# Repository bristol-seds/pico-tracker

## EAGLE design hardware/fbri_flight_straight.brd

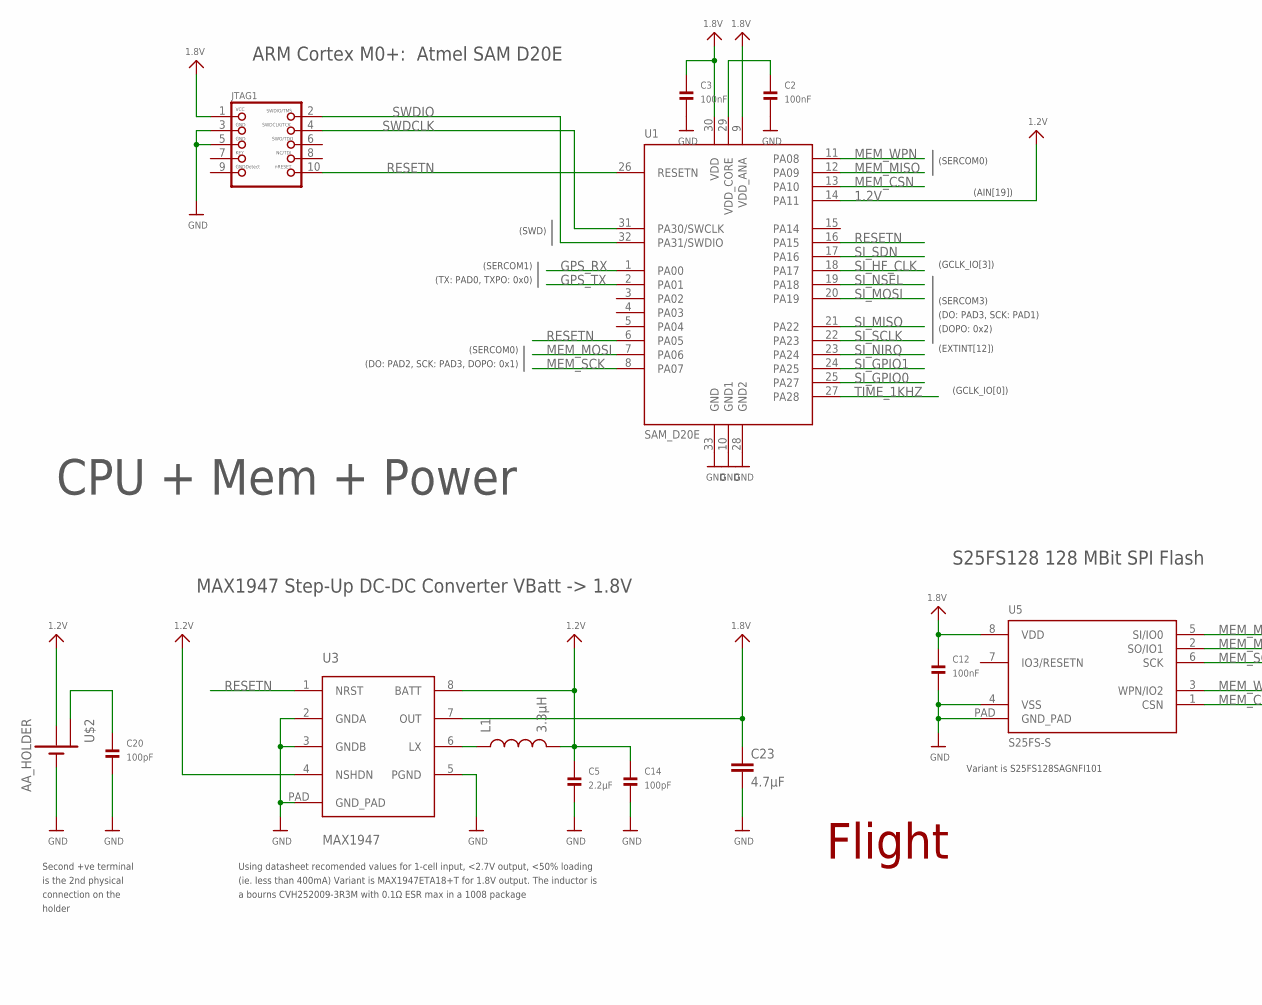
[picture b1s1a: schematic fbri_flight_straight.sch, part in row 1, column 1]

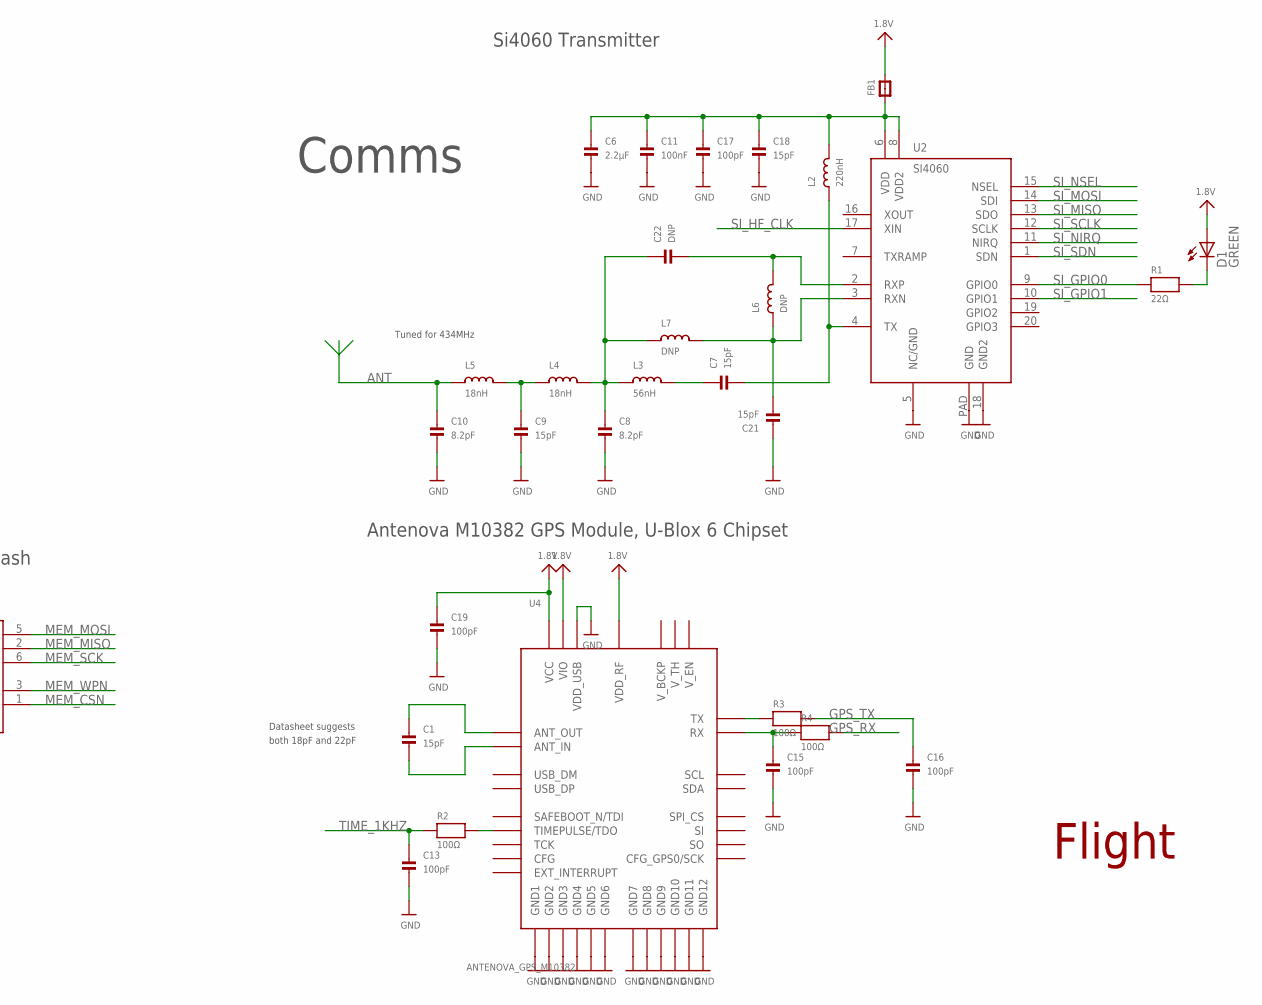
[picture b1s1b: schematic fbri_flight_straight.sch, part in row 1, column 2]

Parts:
C1, C7, C9, C18, C21: 15pF; _0402
C2, C3, C11, C12: 100nF; _0402
C5, C6: 2.2µF; _0402
C8, C10: 8.2pF; _0402
C13, C14, C15, C16, C17, C19, C20: 100pF; _0402
C22: DNP; _0402
C23: 4.7µF; C0603K
D1: GREEN; CHIPLED_0603
FB1: FERRITE_0402; _0402
JTAG1: JTAG-CORTEXM3SMT; 2X05_1.27MM_SMT
L1: 3.3µH; 1007
L2: 220nH; _0402
L3: 56nH; _0402
L4, L5: 18nH; _0402
L6, L7: DNP; _0402
R1: 22Ω; _0402
R2, R3, R4: 100Ω; _0402
U1: SAM_D20E; QFN32_5MM
U2: SI4060; QFN20
U3: MAX1947; TDFN8
U4: ANTENOVA_GPS_M10382
U5: S25FS-S; WSON8
U$2: AA_HOLDER; AA

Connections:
1.2V: C5.1, C14.1, L1.2, U1.14 (PA11), U3.4 (NSHDN), U3.8 (BATT), U$2.+2 (+)
1.8V: C3.1, C12.1, C19.1, C23.1, D1.A, FB1.2, JTAG1.1, U1.9 (VDD_ANA), U1.30 (VDD), U3.7 (OUT), U4.5_VIO (VIO), U4.25_VDD_RF (VDD_RF), U4.27_VCC (VCC), U5.8 (VDD)
ANT: C10.1, L5.1
AN_GPS_RX: C15.1, R4.1, U4.13_RX (RX)
AN_GPS_TX: R3.1, U4.11_TX (TX)
FILTER1: C8.1, C22.1, L3.1, L4.2, L7.1
FILTER2: C9.1, L4.1, L5.2
GND: C2.2, C3.2, C5.2, C6.2, C8.2, C9.2, C10.2, C11.2, C12.2, C13.2, C14.2, C15.2, C16.2, C17.2, C18.2, C19.2, C20.2, C21.1, C23.2, JTAG1.3, JTAG1.5, U1.10 (GND1), U1.28 (GND2), U1.33 (GND), U2.5 (NC/GND), U2.18 (GND2), U2.PAD (GND), U3.2 (GNDA), U3.3 (GNDB), U3.5 (PGND), U3.PAD (GND_PAD), U4.2_GND (GND1), U4.4_GND (GND2), U4.14_GND (GND3), U4.17_GND (GND4), U4.21_GND (GND5), U4.24_GND (GND6), U4.26_GND (GND7), U4.28_GND (GND8), U4.32_VDD_USB (VDD_USB), U4.33_GND (GND9), U4.34_GND (GND10), U4.35_GND (GND11), U4.36_GND (GND12), U5.4 (VSS), U5.PAD (GND_PAD), U$2.-1 (-), U$2.-2 (-)
GPS_ANT_IN: C1.2, U4.1_ANT_IN (ANT_IN)
GPS_ANT_OUT: C1.1, U4.3_ANT_OUT (ANT_OUT)
GPS_RX: R4.2, U1.1 (PA00)
GPS_TX: C16.1, R3.2, U1.2 (PA01)
LED_RES: D1.C, R1.2
LX: L1.1, U3.6 (LX)
MEM_CSN: U1.13 (PA10), U5.1 (CSN)
MEM_MISO: U1.12 (PA09), U5.2 (SO/IO1)
MEM_MOSI: U1.7 (PA06), U5.5 (SI/IO0)
MEM_SCK: U1.8 (PA07), U5.6 (SCK)
MEM_WPN: U1.11 (PA08), U5.3 (WPN/IO2)
unnamed: C20.1, U$2.+1 (+2)
RADIO_VDD: C6.1, C11.1, C17.1, C18.1, FB1.1, L2.2, U2.6 (VDD), U2.8 (VDD2)
RESETN: JTAG1.10, U1.6 (PA05), U1.16 (PA15), U1.26 (RESETN), U3.1 (NRST)
RF_OUT: C7.2, L2.1, U2.4 (TX)
RXN: C21.2, L6.1, L7.2, U2.3 (RXN)
RXP: C22.2, L6.2, U2.2 (RXP)
SI_GPIO0: R1.1, U1.25 (PA27), U2.9 (GPIO0)
SI_GPIO1: U1.24 (PA25), U2.10 (GPIO1)
SI_HF_CLK: U1.18 (PA17), U2.17 (XIN)
SI_MISO: U1.21 (PA22), U2.13 (SDO)
SI_MOSI: U1.20 (PA19), U2.14 (SDI)
SI_NIRQ: U1.23 (PA24), U2.11 (NIRQ)
SI_NSEL: U1.19 (PA18), U2.15 (NSEL)
SI_SCLK: U1.22 (PA23), U2.12 (SCLK)
SI_SDN: U1.17 (PA16), U2.1 (SDN)
SWDCLK: JTAG1.4, U1.31 (PA30/SWCLK)
SWDIO: JTAG1.2, U1.32 (PA31/SWDIO)
TANK: C7.1, L3.2
TIME_1KHZ: C13.1, R2.1, U1.27 (PA28)
TIME_1KHZ_DRIVE: R2.2, U4.23_TIMEPULSE/TDO (TIMEPULSE/TDO)
VDD_CORE: C2.1, U1.29 (VDD_CORE)

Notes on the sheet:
ARM Cortex M0+: Atmel SAM D20E
(SERCOM3)
(SWD)
(GCLK_IO[0])
Using datasheet recomended values for 1-cell input, <2.7V output, <50% loading (ie. less than 400mA) Variant is MAX1947ETA18+T for 1.8V output. The inductor is a bourns CVH252009-3R3M with 0.1Ω ESR max in a 1008 package
(SERCOM0)
(EXTINT[12])
(DO: PAD3, SCK: PAD1)
(DOPO: 0x2)
(DO: PAD2, SCK: PAD3, DOPO: 0x1)
(GCLK_IO[3])
(SERCOM1)
(TX: PAD0, TXPO: 0x0)
MAX1947 Step-Up DC-DC Converter VBatt -> 1.8V
(AIN[19])
S25FS128 128 MBit SPI Flash
Variant is S25FS128SAGNFI101
Antenova M10382 GPS Module, U-Blox 6 Chipset
Si4060 Transmitter
Tuned for 434MHz
CPU + Mem + Power
Comms
Flight
Datasheet suggests both 18pF and 22pF
Second +ve terminal is the 2nd physical connection on the holder

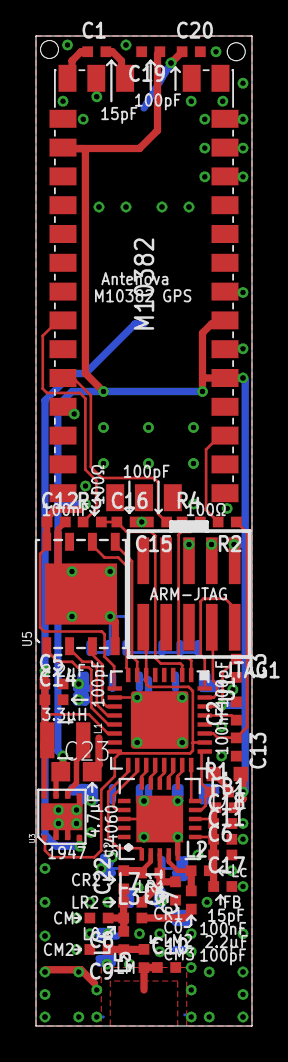
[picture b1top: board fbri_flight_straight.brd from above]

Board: 2 copper layers, 12.0 x 55.0 mm, 42 parts (1 on the bottom side), 40 nets.

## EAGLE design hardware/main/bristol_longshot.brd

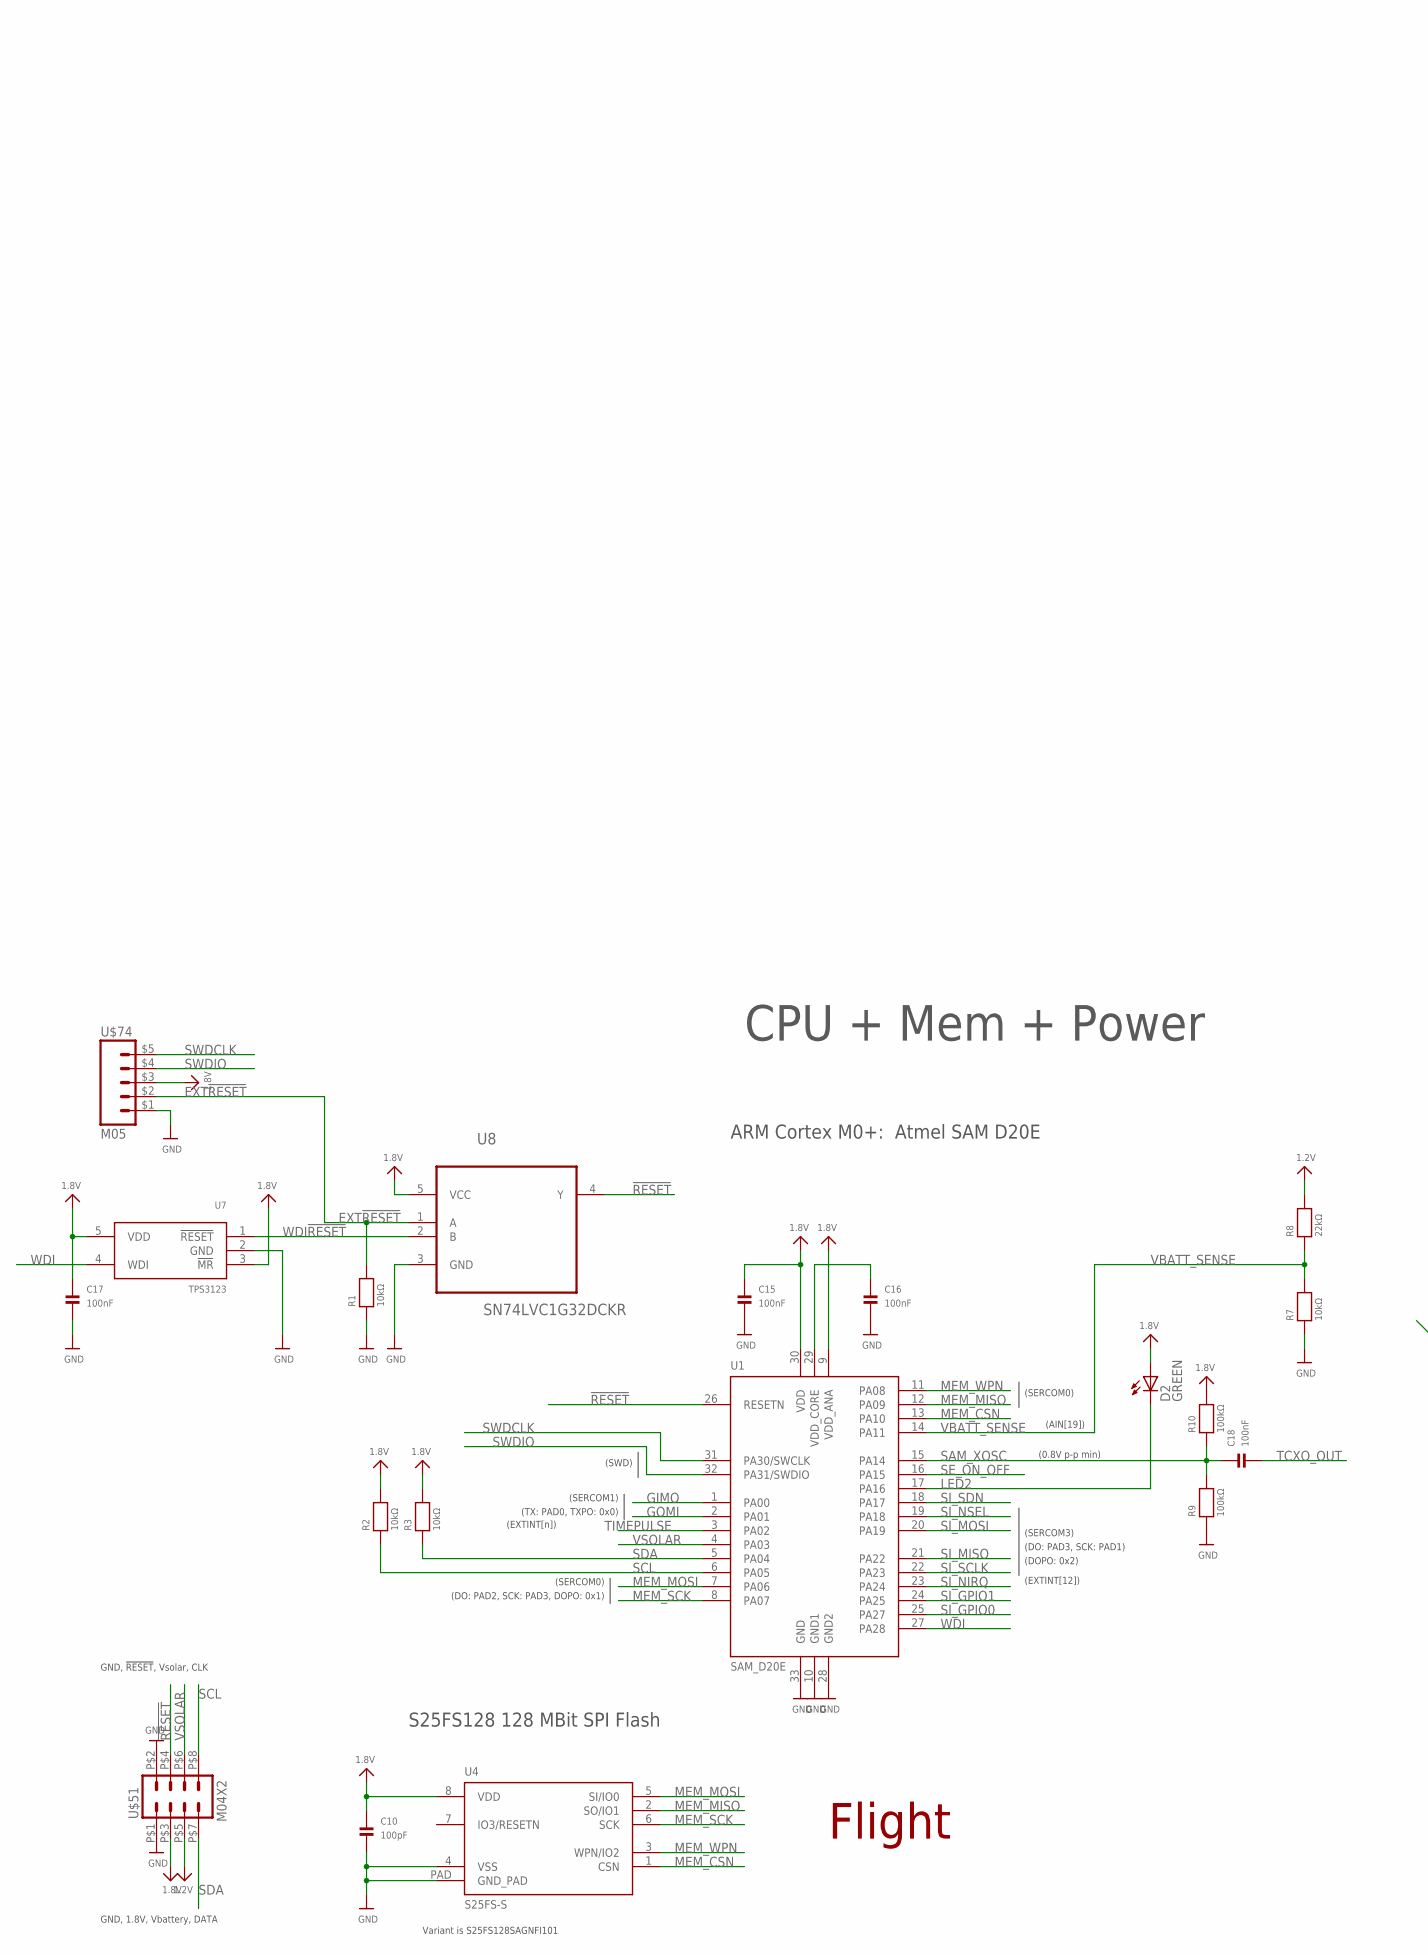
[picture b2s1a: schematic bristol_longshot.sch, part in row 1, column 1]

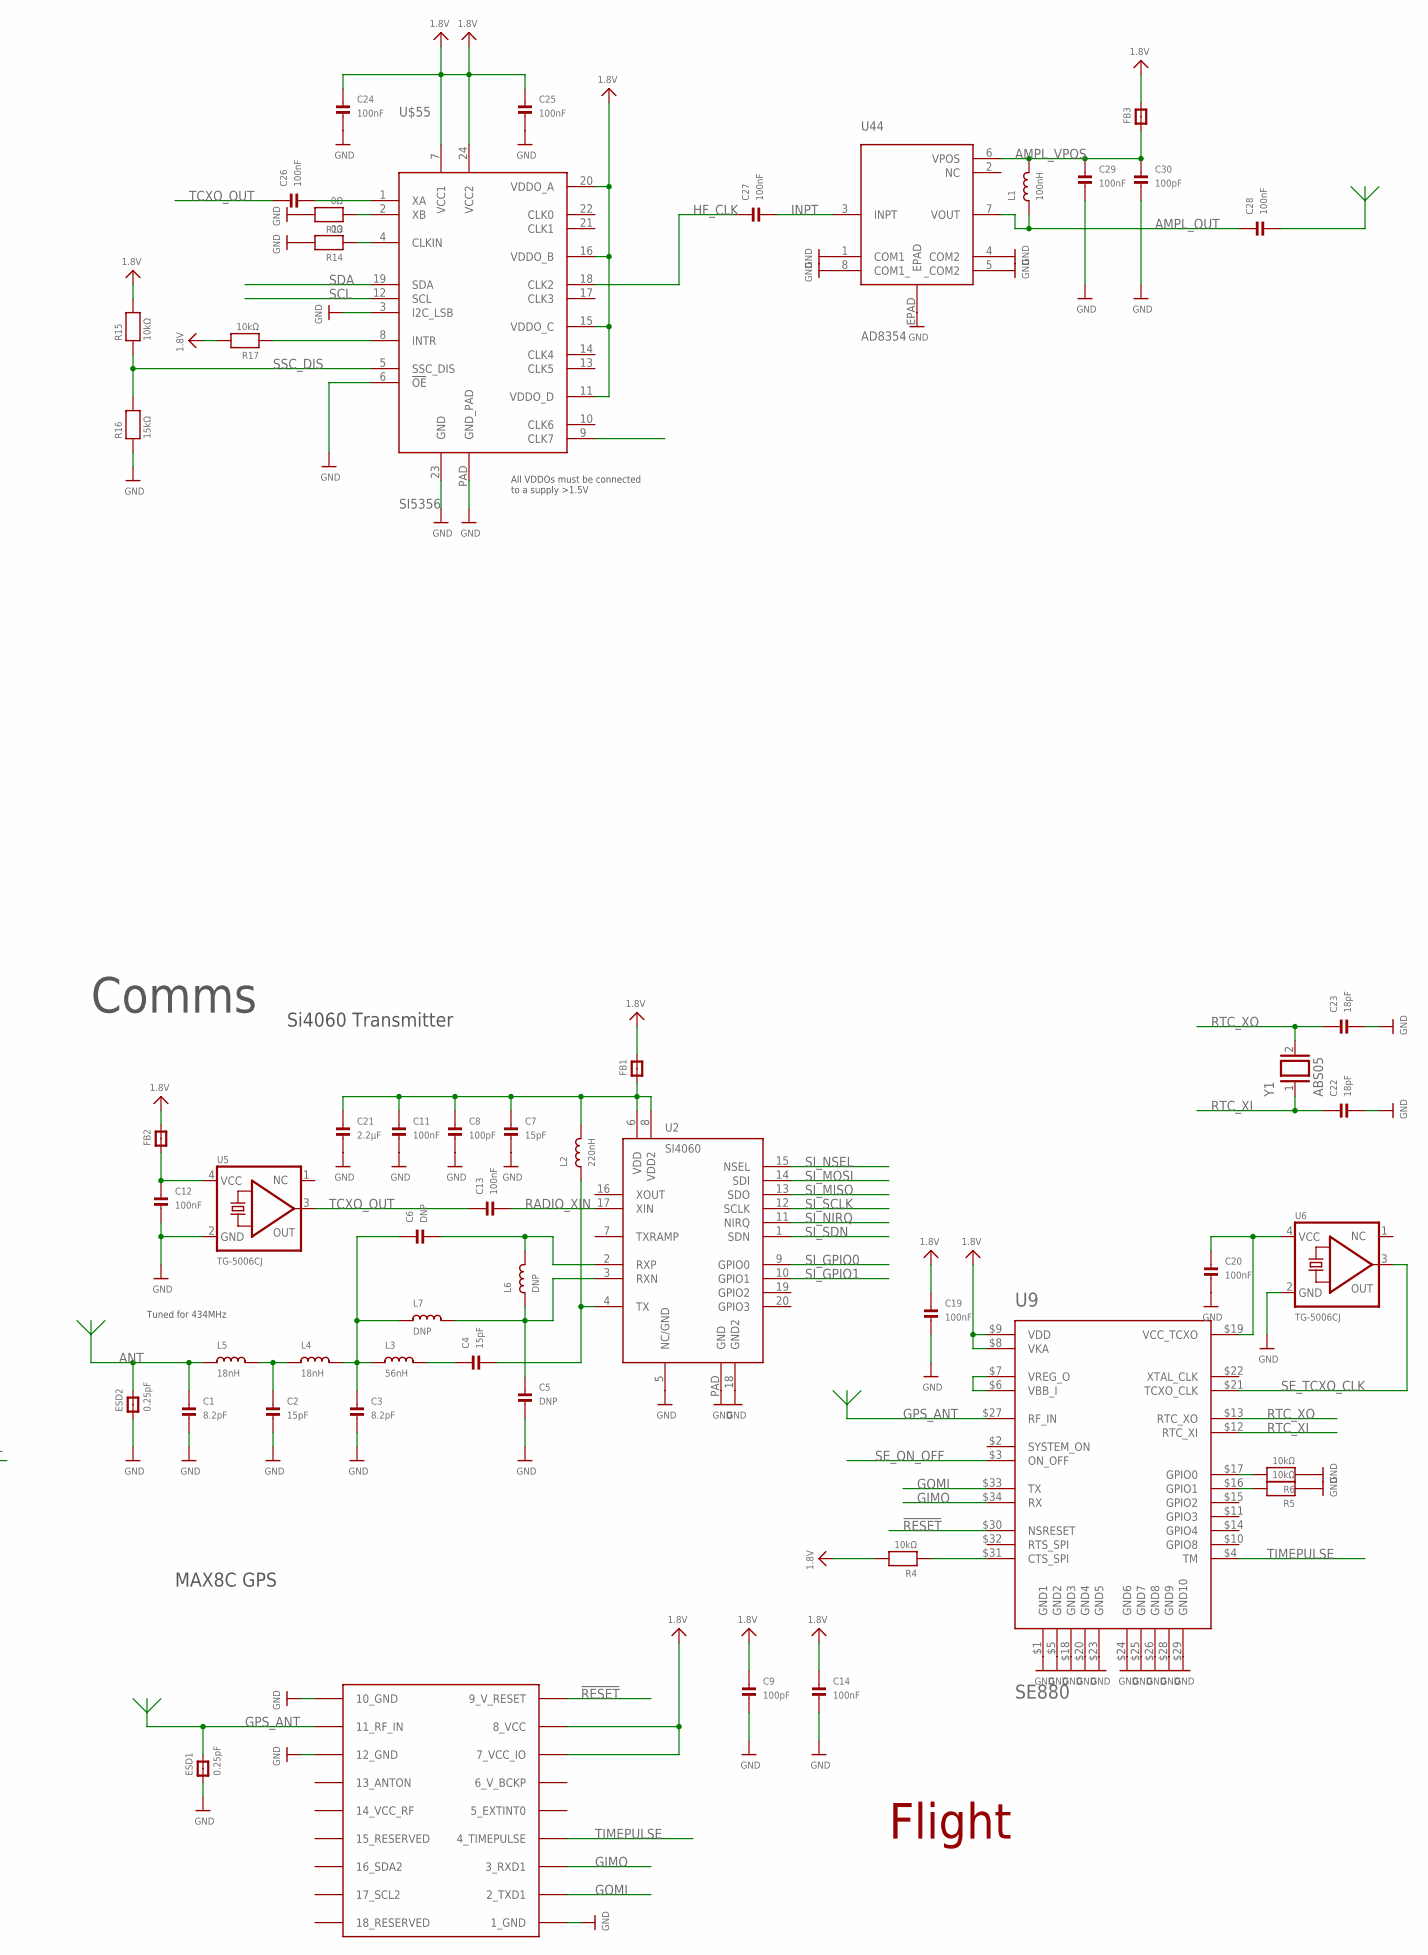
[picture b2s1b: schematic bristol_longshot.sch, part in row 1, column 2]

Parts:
C1, C3: 8.2pF; _0402
C2, C4, C7: 15pF; _0402
C5, C6: DNP; _0402
C8, C9, C10, C30: 100pF; _0402
C11, C12, C13, C14, C15, C16, C17, C18, C19, C20, C24, C25, C26, C27, C28, C29: 100nF; _0402
C21: 2.2µF; _0402
C22, C23: 18pF; _0402
D2: GREEN; CHIPLED_0603
ESD1, ESD2: 0.25pF; _0603MP
FB1, FB2, FB3: FERRITE_0402; _0402
L1: 100nH; _0402
L2: 220nH; _0402
L3: 56nH; _0402
L4, L5: 18nH; _0402
L6, L7: DNP; _0402
R1, R2, R3, R4, R5, R6, R7, R15, R17: 10kΩ; _0402
R8: 22kΩ; _0402
R9, R10: 100kΩ; _0402
R13, R14: 0Ω; _0402
R16: 15kΩ; _0402
U1: SAM_D20E; QFN32_5MM
U2: SI4060; QFN20
U3: UBLOX_MAX
U4: S25FS-S; WSON8
U5, U6: TG-5006CJ; TC-5006CJ
U7: TPS3123; SOT23-5
U8: SN74LVC1G32DCKR; SOT65P210X110-5N
U9: SE880
U44: AD8354; LFCSP_VD_8
U$51: M04X2
U$55: SI5356; QFN24_4MM
U$74: M05; M05_SIDE
Y1: ABS05

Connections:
1.2V: R8.2, U$51.P$5 (5)
1.8V: C9.1, C10.1, C14.1, C15.1, C17.1, C19.1, C24.1, C25.1, D2.A, FB1.2, FB2.2, FB3.2, R2.2, R3.2, R4.2, R10.2, R15.2, R17.2, U1.9 (VDD_ANA), U1.30 (VDD), U3.7_VCC_IO, U3.8_VCC, U4.8 (VDD), U7.3 (!MR), U7.5 (VDD), U8.5 (VCC), U9.$8 (VKA), U9.$9 (VDD), U$51.P$3 (3), U$55.7 (VCC1), U$55.11 (VDDO_D), U$55.15 (VDDO_C), U$55.16 (VDDO_B), U$55.20 (VDDO_A), U$55.24 (VCC2), U$74.$3 (3)
!RESET: U1.26 (RESETN), U3.9_V_RESET, U8.4 (Y), U9.$30 (NSRESET), U$51.P$4 (4)
AMPL_OUT: C28.1, L1.1, U44.7 (VOUT)
AMPL_VPOS: C29.1, C30.1, FB3.1, L1.2, U44.6 (VPOS)
ANT: C1.1, ESD2.2, L5.1
CLKIN: R14.1, U$55.4 (CLKIN)
EXT!RESET: R1.2, U8.1 (A), U$74.$2 (2)
FILTER1: C3.1, C6.1, L3.1, L4.2, L7.1
FILTER2: C2.1, L4.1, L5.2
GIMO: U1.1 (PA00), U3.3_RXD1, U9.$34 (RX)
GND: C1.2, C2.2, C3.2, C5.2, C7.2, C8.2, C9.2, C10.2, C11.2, C12.2, C14.2, C15.2, C16.2, C17.2, C19.2, C20.2, C21.2, C22.2, C23.2, C24.2, C25.2, C29.2, C30.2, ESD1.1, ESD2.1, R1.1, R5.1, R6.1, R7.1, R9.1, R13.2, R14.2, R16.1, U1.10 (GND1), U1.28 (GND2), U1.33 (GND), U2.5 (NC/GND), U2.18 (GND2), U2.PAD (GND), U3.1_GND, U3.10_GND, U3.12_GND, U4.4 (VSS), U4.PAD (GND_PAD), U5.2 (GND), U6.2 (GND), U7.2 (GND), U8.3 (GND), U9.$1 (GND1), U9.$5 (GND2), U9.$18 (GND3), U9.$20 (GND4), U9.$23 (GND5), U9.$24 (GND6), U9.$25 (GND7), U9.$26 (GND8), U9.$28 (GND9), U9.$29 (GND10), U44.1 (COM1), U44.4 (COM2), U44.5 (_COM2), U44.8 (COM1_), U44.EPAD, U$51.P$1 (1), U$51.P$2 (2), U$55.3 (I2C_LSB), U$55.6 (!OE), U$55.23 (GND), U$55.PAD (GND_PAD), U$74.$1 (1)
GOMI: U1.2 (PA01), U3.2_TXD1, U9.$33 (TX)
GPS_ANT: ESD1.2, U3.11_RF_IN, U9.$27 (RF_IN)
HF_ANT: C28.2
HF_CLK: C27.1, U$55.18 (CLK2)
INPT: C27.2, U44.3 (INPT)
INTR: R17.1, U$55.8 (INTR)
LED2: D2.C, U1.17 (PA16)
MEM_CSN: U1.13 (PA10), U4.1 (CSN)
MEM_MISO: U1.12 (PA09), U4.2 (SO/IO1)
MEM_MOSI: U1.7 (PA06), U4.5 (SI/IO0)
MEM_SCK: U1.8 (PA07), U4.6 (SCK)
MEM_WPN: U1.11 (PA08), U4.3 (WPN/IO2)
unnamed: U9.$6 (VBB_I), U9.$7 (VREG_O)
unnamed: R6.2, U9.$17 (GPIO0)
unnamed: R4.1, U9.$31 (CTS_SPI)
unnamed: R5.2, U9.$16 (GPIO1)
RADIO_VDD: C7.1, C8.1, C11.1, C21.1, FB1.1, L2.2, U2.6 (VDD), U2.8 (VDD2)
RADIO_XIN: C13.2, U2.17 (XIN)
RF_OUT: C4.2, L2.1, U2.4 (TX)
RTC_XI: C22.1, U9.$12 (RTC_XI), Y1.1
RTC_XO: C23.1, U9.$13 (RTC_XO), Y1.2
RXN: C5.1, L6.1, L7.2, U2.3 (RXN)
RXP: C6.2, L6.2, U2.2 (RXP)
SAM_XOSC: C18.1, R9.2, R10.1, U1.15 (PA14)
SCL: R2.1, U1.6 (PA05), U$51.P$8 (8), U$55.12 (SCL)
SDA: R3.1, U1.5 (PA04), U$51.P$7 (7), U$55.19 (SDA)
SE_ON_OFF: U1.16 (PA15), U9.$3 (ON_OFF)
SE_TCXO_CLK: U6.3 (OUT), U9.$21 (TCXO_CLK)
SE_VCO_TCXO: C20.1, U6.4 (VCC), U9.$19 (VCC_TCXO)
SI_GPIO0: U1.25 (PA27), U2.9 (GPIO0)
SI_GPIO1: U1.24 (PA25), U2.10 (GPIO1)
SI_MISO: U1.21 (PA22), U2.13 (SDO)
SI_MOSI: U1.20 (PA19), U2.14 (SDI)
SI_NIRQ: U1.23 (PA24), U2.11 (NIRQ)
SI_NSEL: U1.19 (PA18), U2.15 (NSEL)
SI_SCLK: U1.22 (PA23), U2.12 (SCLK)
SI_SDN: U1.18 (PA17), U2.1 (SDN)
SSC_DIS: R15.1, R16.2, U$55.5 (SSC_DIS)
SWDCLK: U1.31 (PA30/SWCLK), U$74.$5 (5)
SWDIO: U1.32 (PA31/SWDIO), U$74.$4 (4)
TANK: C4.1, L3.2
TCXO_OUT: C13.1, C18.2, C26.1, U5.3 (OUT)
TCXO_VDD: C12.1, FB2.1, U5.4 (VCC)
TIMEPULSE: U1.3 (PA02), U3.4_TIMEPULSE, U9.$4 (TM)
VBATT_SENSE: R7.2, R8.1, U1.14 (PA11)
VDD_CORE: C16.1, U1.29 (VDD_CORE)
VSOLAR: U1.4 (PA03), U$51.P$6 (6)
WDI: U1.27 (PA28), U7.4 (WDI)
WDI!RESET: U7.1 (!RESET), U8.2 (B)
XA: C26.2, U$55.1 (XA)
XB: R13.1, U$55.2 (XB)

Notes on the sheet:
ARM Cortex M0+: Atmel SAM D20E
(SERCOM3)
(SWD)
(SERCOM0)
(EXTINT[12])
(DO: PAD3, SCK: PAD1)
(DOPO: 0x2)
(DO: PAD2, SCK: PAD3, DOPO: 0x1)
(SERCOM1)
(TX: PAD0, TXPO: 0x0)
(AIN[19])
S25FS128 128 MBit SPI Flash
Variant is S25FS128SAGNFI101
MAX8C GPS
Si4060 Transmitter
Tuned for 434MHz
CPU + Mem + Power
Comms
Flight
(EXTINT[n])
(0.8V p-p min)
GND, !RESET!, Vsolar, CLK
GND, 1.8V, Vbattery, DATA
All VDDOs must be connected to a supply >1.5V

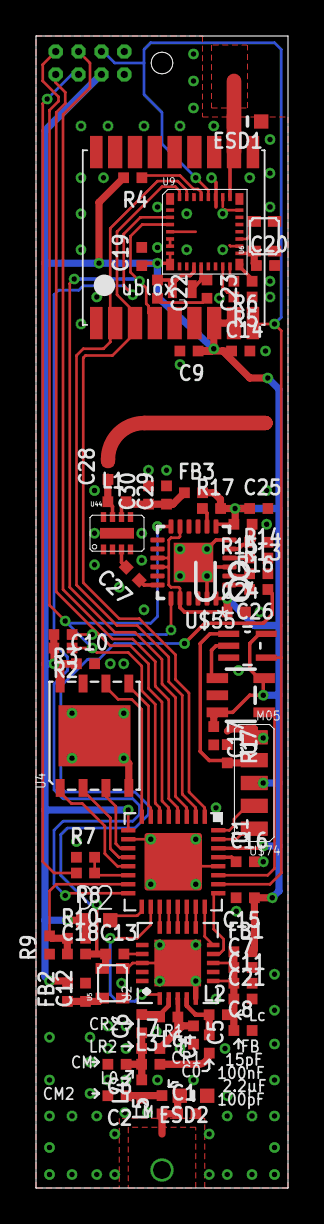
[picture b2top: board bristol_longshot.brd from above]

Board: 2 copper layers, 14.0 x 64.0 mm, 72 parts (1 on the bottom side), 62 nets.

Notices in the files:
parts and their libraries:
SparkFun: Licensing: CC v3.0 Share-Alike You are welcome to use this library for commercial purposes.
microbuilder_v3: This work is placed in the public domain, and may be freely used for commercial and non-commercial work with the following conditions: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
